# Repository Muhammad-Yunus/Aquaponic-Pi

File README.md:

# Aquaponic-Pi

### Diagram block and Pin Mapping

##### One Wire Pin (4x DS18B20 Digital Temperature Sensor):
- Data -> GPIO13 RPI Zero 

##### Water Level Sensor
- WL Sensor A -> GPIO22 RPI Zero
- WL Sensor B -> GPIO27 RPI Zero

##### Selenoid Valve
- SV A -> GPIO19 RPI Zero
- SV B -> GPIO26 RPI Zero

##### TDS Probe to analog interface to PCF8591
- Left analog TDS -> A0
- Right analog TDS -> A1

### Content in this repo :
- Board Schematics (Cad Soft Eagle)
- Board Layout (Cad Soft Eagle)
- Python program :
    a. DS18B20
    b. PCF8591
    c. Selenoid Valve
    d. Water Level
    e. TDS 

##### Design And Developed By :
- [Legendre Technology](https://www.facebook.com/LegendreTechnology/)
- (Ziath & Robby) PRC Dept.of Physics Bogor Agricultural University

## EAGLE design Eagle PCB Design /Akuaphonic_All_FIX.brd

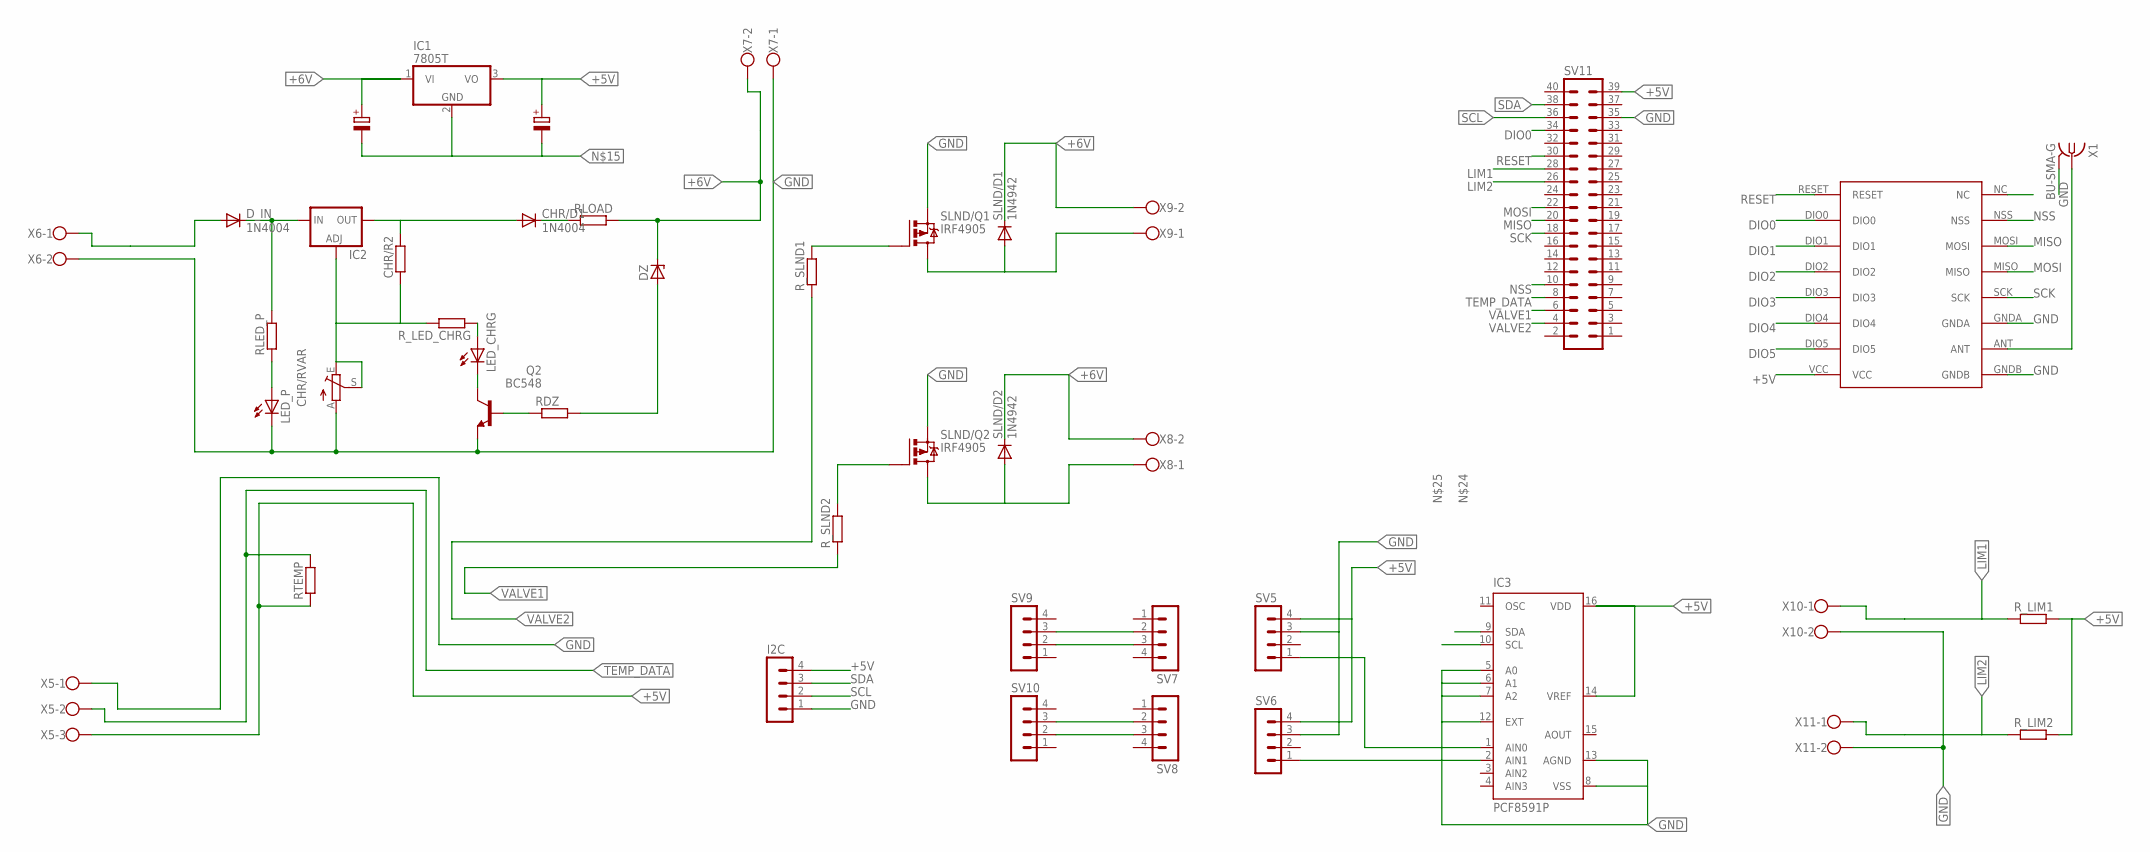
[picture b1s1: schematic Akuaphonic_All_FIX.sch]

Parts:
CHR/D1: 1N4004; DO41-10
CHR/R2: R0207/10; 0207/10
CHR/RVAR: TRIM_EU-B25P; B25P
DZ: ZENER-DIODEDO35Z10; DO35Z10
D_IN: 1N4004; DO41-10
I2C: MA04-1
IC1: 7805T; TO220H
IC2: LM317TL; 317TL
IC3: PCF8591P; DIL16
LED_CHRG: LED3MM
LED_P: LED3MM
Q2: BC548; TO92-EBC
RDZ: R0207/10; 0207/10
RLED_P: R0207/10; 0207/10
RLOAD: R0207/10; 0207/10
RTEMP: R0207/10; 0207/10
R_LED_CHRG: R0207/10; 0207/10
R_LIM1, R_LIM2: R0207/10; 0207/10
R_SLND1, R_SLND2: R0207/10; 0207/10
SLND/D1, SLND/D2: 1N4942; DO41-10
SLND/Q1, SLND/Q2: IRF4905; TO220BH
SV5, SV6, SV7, SV8, SV9, SV10: MA04-1
SV11: MA20-2
U$1: RFM69HW; RFM
X1: BU-SMA-G
X5: W237-103
X6, X7, X8, X9, X10, X11: W237-102

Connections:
+5V: I2C.4, IC1.3 (VO), IC3.14 (VREF), IC3.16 (VDD), RTEMP.1, R_LIM1.2, R_LIM2.2, SV5.4, SV6.4, SV11.39, U$1.VCC, X5.3
+6V: DZ.C, IC1.1 (VI), RLOAD.2, SLND/D1.C, SLND/D2.C, X7.2, X8.2, X9.2
DIO0: SV11.34, U$1.DIO0
DIO1: U$1.DIO1
DIO2: U$1.DIO2
DIO3: U$1.DIO3
DIO4: U$1.DIO4
DIO5: U$1.DIO5
DLOAD: CHR/D1.C, RLOAD.1
GND: CHR/RVAR.A, I2C.1, IC3.5 (A0), IC3.6 (A1), IC3.7 (A2), IC3.8 (VSS), IC3.12 (EXT), IC3.13 (AGND), LED_P.K (C), Q2.E, SLND/Q1.S, SLND/Q2.S, SV5.3, SV6.3, SV11.35, U$1.GNDA, U$1.GNDB, X1.2, X1.3 (2), X1.4 (2), X1.5 (2), X5.1, X6.2, X7.1, X10.2, X11.2
LIM1: R_LIM1.1, SV11.28, X10.1
LIM2: R_LIM2.1, SV11.26, X11.1
LM143: CHR/R2.1, CHR/RVAR.E, CHR/RVAR.S, IC2.1 (ADJ), R_LED_CHRG.2
MISO: SV11.20, U$1.MOSI
MOSI: SV11.22, U$1.MISO
unnamed: D_IN.A, X6.1
unnamed: LED_CHRG.K (C), Q2.C
unnamed: U$1.ANT, X1.1
unnamed: D_IN.C, IC2.3 (IN), RLED_P.2
unnamed: CHR/D1.A, CHR/R2.2, IC2.2 (OUT)
unnamed: SLND/D1.A, SLND/Q1.D, X9.1
unnamed: LED_P.A, RLED_P.1
unnamed: Q2.B, RDZ.1
unnamed: R_SLND1.2, SLND/Q1.G
unnamed: LED_CHRG.A, R_LED_CHRG.1
unnamed: SLND/D2.A, SLND/Q2.D, X8.1
unnamed: SV7.2, SV9.3
unnamed: R_SLND2.2, SLND/Q2.G
unnamed: SV7.3, SV9.2
unnamed: DZ.A, RDZ.2
unnamed: SV8.2, SV10.3
unnamed: SV8.3, SV10.2
unnamed: IC3.1 (AIN0), SV5.1
unnamed: IC3.2 (AIN1), SV6.1
NSS: SV11.10, U$1.NSS
RESET: SV11.30, U$1.RESET
SCK: SV11.18, U$1.SCK
SCL: I2C.2, SV11.36
SDA: I2C.3, SV11.38
TEMP_DATA: RTEMP.2, SV11.8, X5.2
VALVE1: R_SLND2.1, SV11.6
VALVE2: R_SLND1.1, SV11.4

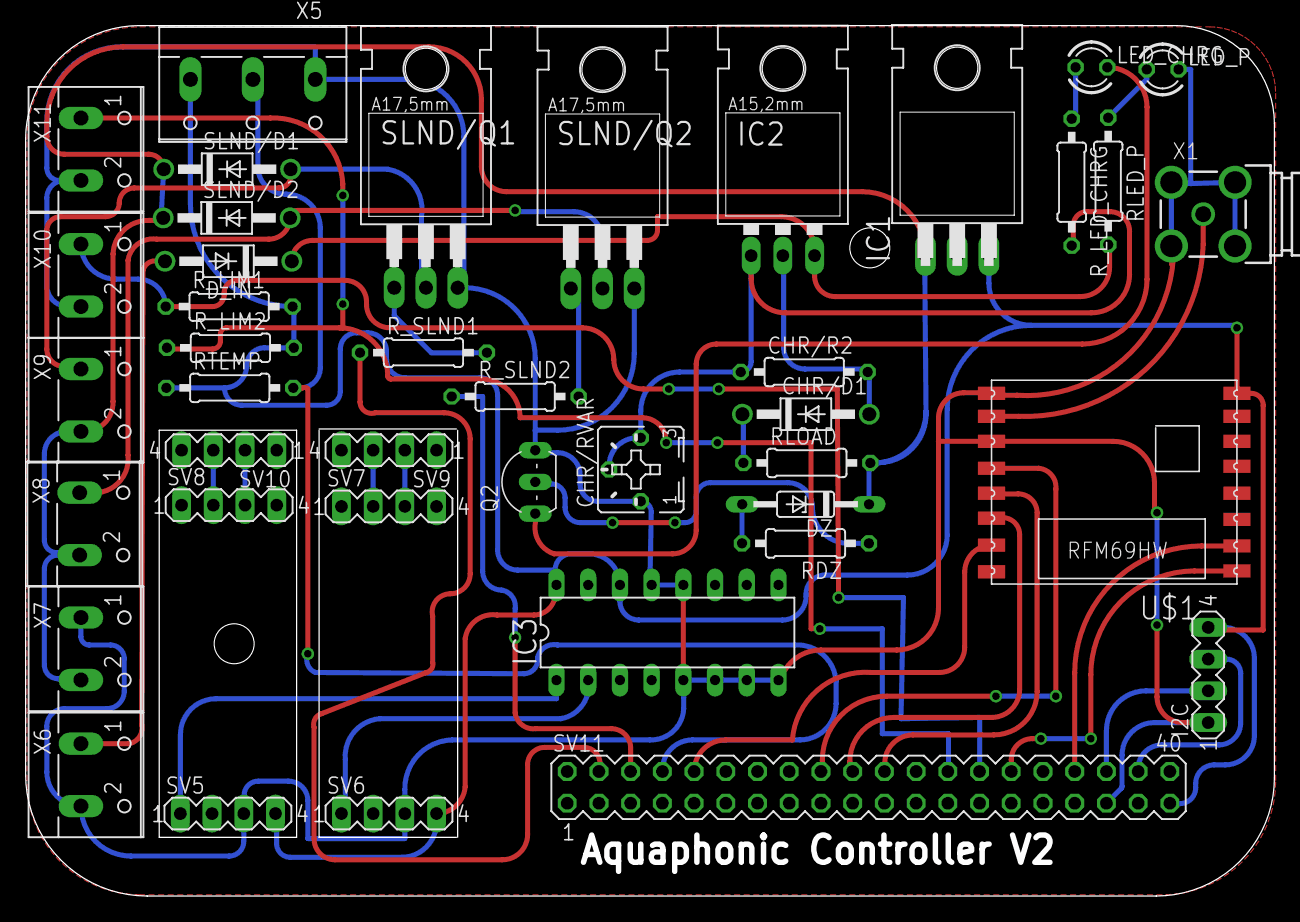
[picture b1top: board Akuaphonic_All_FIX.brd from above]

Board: 2 copper layers, 100.0 x 69.7 mm, 41 parts (0 on the bottom side), 37 nets.
